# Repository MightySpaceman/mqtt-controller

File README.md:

# mqtt-controller (WIP: Code coming soon.)
A D1 Mini carrier board for controlling MQTT devices, with 5 buttons and space for a 128x64 SSD1306 OLED display. 

## Components:
1x Wemos D1 mini developement board (or offbrand version)
1x 128x64 i2c SSD1306 OLED display
5x 6mm SMD-mounted tactile switches
2x 2 by 10 header socket (for mounting microcontroller)
1x 4-pin single row header socket (for mounting display)

(Note: header pins are optional, as the microcontroller/display can be soldered directly onto the board if that is more convenient)

## Screenshots

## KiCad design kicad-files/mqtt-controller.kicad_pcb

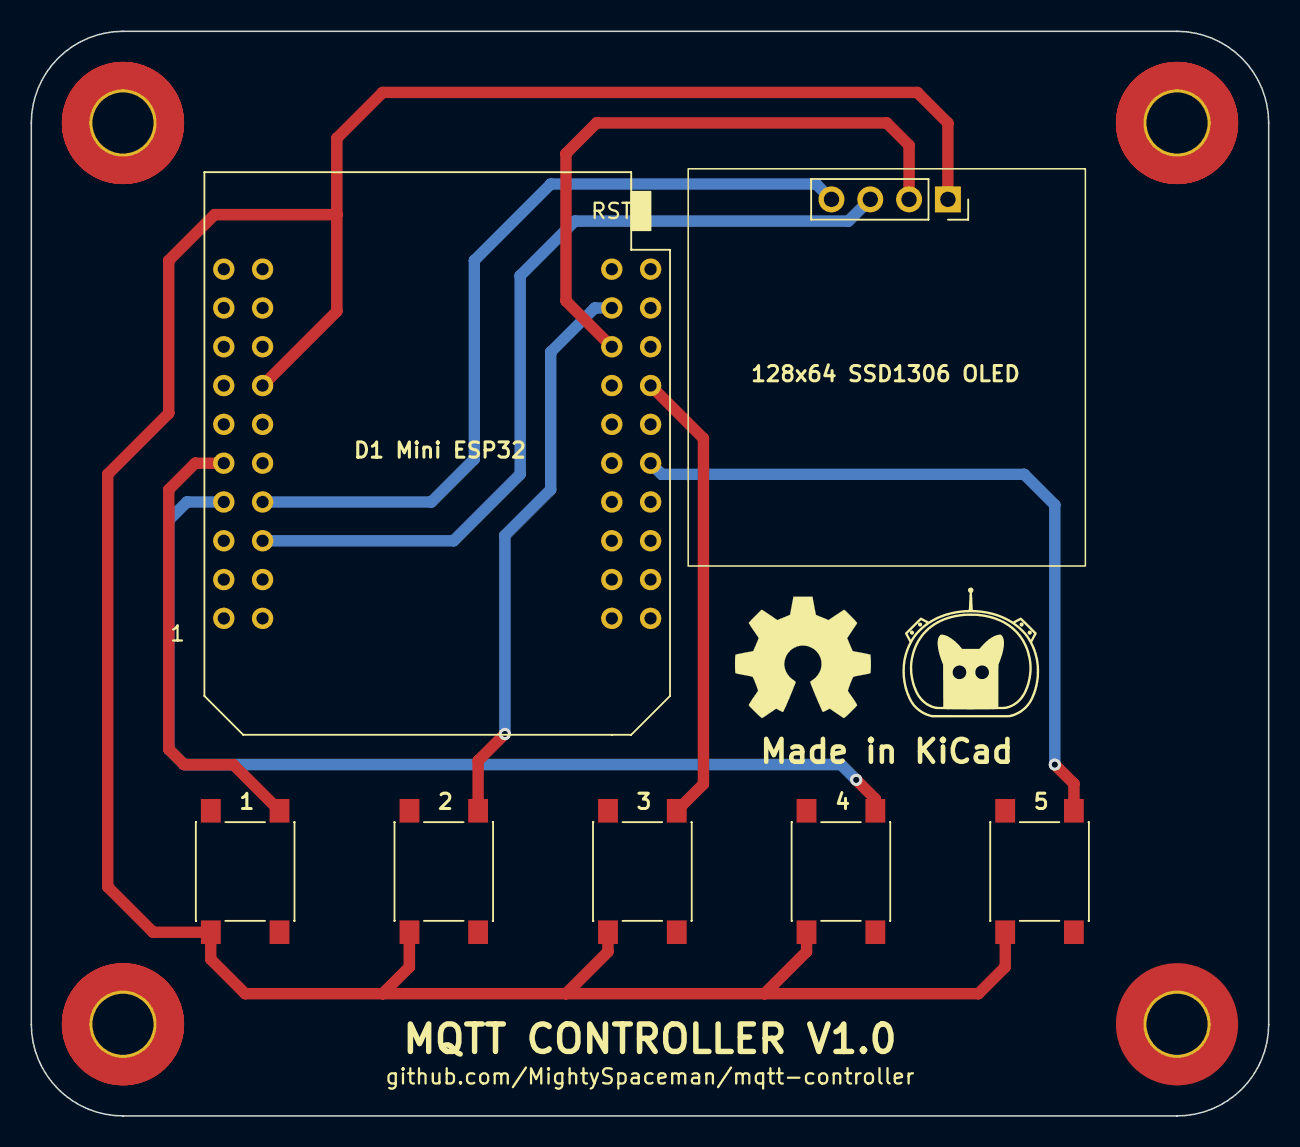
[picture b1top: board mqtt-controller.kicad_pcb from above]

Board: 2 copper layers, 81.0 x 71.0 mm, 7 parts (0 on the bottom side), 9 nets.

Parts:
1: SW_Push; SW_Push_1P1T_NO_6x6mm_H9.5mm
J1: Conn_01x04_Pin; PinSocket_1x04_P2.54mm_Vertical
SW1, SW3, SW4, SW5: SW_Push; SW_Push_1P1T_NO_6x6mm_H9.5mm
U2: mini_esp32; ESP32_mini

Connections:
unnamed: 1.1, J1.1, SW1.1, SW3.1, SW4.1, SW5.1, U2.33 (GND)
unnamed: J1.2, U2.16 (3V3)
unnamed: J1.3, U2.25 (IO_22/D1/SCL)
unnamed: J1.4, U2.27 (IO_21/D2/SDA)
unnamed: SW1.2, U2.30 (IO_12/TDI)
unnamed: 1.2, U2.18 (IO_13/TCK)
unnamed: SW3.2, U2.13 (IO_14/TMS)
unnamed: SW4.2, U2.28 (IO_32)
unnamed: SW5.2, U2.9 (IO_33)
